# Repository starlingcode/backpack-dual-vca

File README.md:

# backpack-dual-vca
Dual 2164 VCA with precision 5V reference

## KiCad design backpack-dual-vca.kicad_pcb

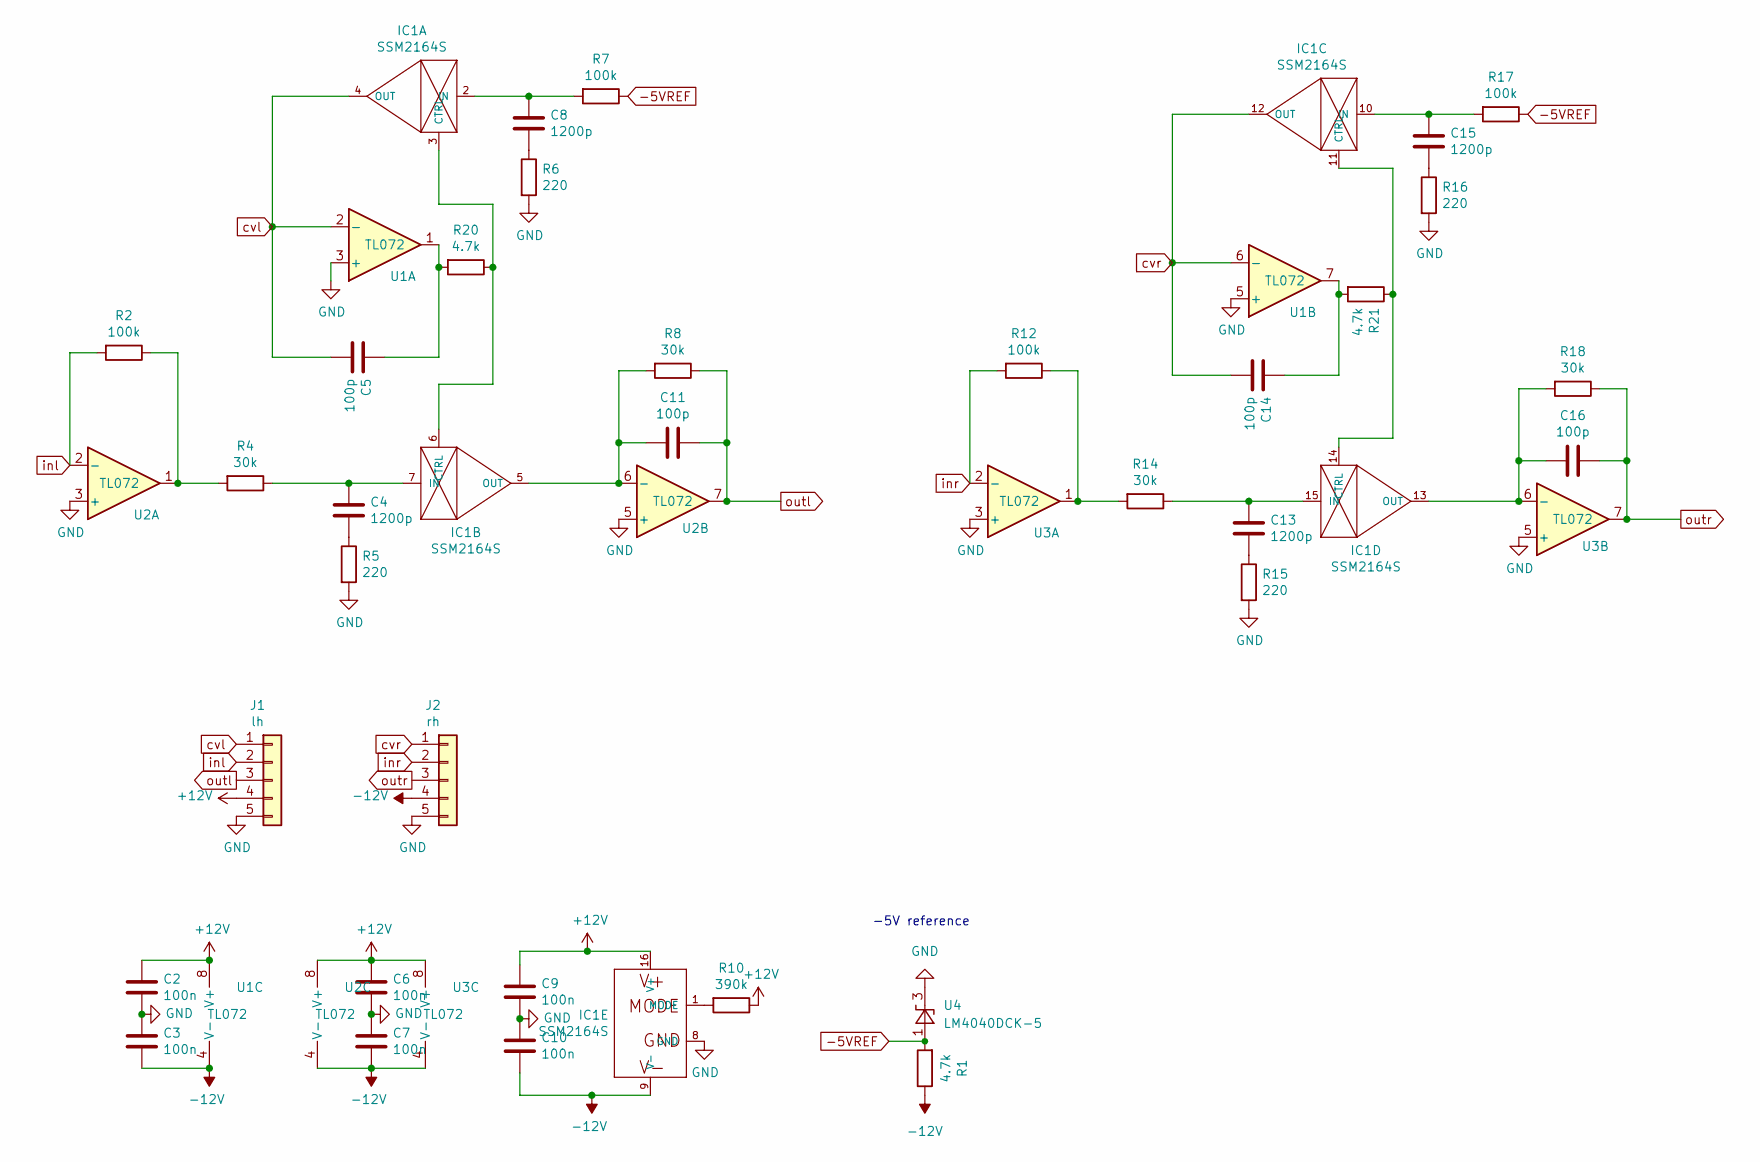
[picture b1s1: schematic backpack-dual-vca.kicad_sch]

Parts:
C2, C3, C6, C7, C9, C10: 100n; C_0402_1005Metric
C4, C8, C13, C15: 1200p; C_0402_1005Metric
C5, C11, C14, C16: 100p; C_0402_1005Metric
IC1: SSM2164S; SOIC-16_3.9x9.9mm_P1.27mm
J1: lh; PinSocket_1x05_P2.54mm_Vertical
J2: rh; PinSocket_1x05_P2.54mm_Vertical
R1, R20, R21: 4.7k; R_0402_1005Metric
R2, R7, R12, R17: 100k; R_0402_1005Metric
R4, R8, R14, R18: 30k; R_0402_1005Metric
R5, R6, R15, R16: 220; R_0402_1005Metric
R10: 390k; R_0402_1005Metric
U1, U2, U3: TL072; VSSOP-8_3.0x3.0mm_P0.65mm
U4: LM4040DCK-5; SOT-353_SC-70-5

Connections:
+12V: C2.1, C6.1, C9.1, IC1.16 (V+), J1.4, R10.1, U1.8 (V+), U2.8 (V+), U3.8 (V+)
-5VREF: R1.2, R7.1, R17.1, U4.1 (A)
-12V: C3.2, C7.2, C10.2, IC1.9 (V-), J2.4, R1.1, U1.4 (V-), U2.4 (V-), U3.4 (V-)
GND: C2.2, C3.1, C6.2, C7.1, C9.2, C10.1, IC1.8 (GND), J1.5, J2.5, R5.2, R6.2, R15.2, R16.2, U1.3 (+), U1.5 (+), U2.3 (+), U2.5 (+), U3.3 (+), U3.5 (+), U4.3 (K)
unnamed: C4.2, R5.1
unnamed: C5.1, R20.2, U1.1
unnamed: C8.2, R6.1
unnamed: C13.2, R15.1
unnamed: C14.1, R21.2, U1.7
unnamed: C15.2, R16.1
unnamed: IC1.3 (CTRL), IC1.6 (CTRL), R20.1
unnamed: C8.1, IC1.2 (IN), R7.2
unnamed: C4.1, IC1.7 (IN), R4.1
unnamed: C11.2, IC1.5 (OUT), R8.2, U2.6 (-)
unnamed: IC1.11 (CTRL), IC1.14 (CTRL), R21.1
unnamed: C15.1, IC1.10 (IN), R17.2
unnamed: C13.1, IC1.15 (IN), R14.1
unnamed: C16.2, IC1.13 (OUT), R18.2, U3.6 (-)
unnamed: IC1.1 (MODE), R10.2
unnamed: R2.1, R4.2, U2.1
unnamed: R12.1, R14.2, U3.1
cvl: C5.2, IC1.4 (OUT), J1.1, U1.2 (-)
cvr: C14.2, IC1.12 (OUT), J2.1, U1.6 (-)
inl: J1.2, R2.2, U2.2 (-)
inr: J2.2, R12.2, U3.2 (-)
outl: C11.1, J1.3, R8.1, U2.7
outr: C16.1, J2.3, R18.1, U3.7

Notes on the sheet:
-5V reference

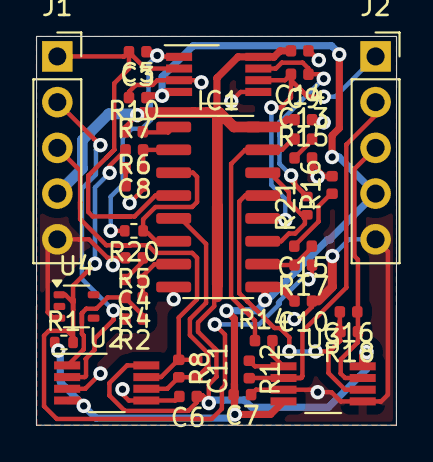
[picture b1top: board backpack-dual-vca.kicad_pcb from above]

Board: 2 copper layers, 20.0 x 21.6 mm, 37 parts (0 on the bottom side), 27 nets.

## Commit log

2024-11-15 Create LICENSE
2024-11-15 add backups folder to .gitignore
2024-11-15 removed cruft

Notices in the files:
backpack-dual-vca.kicad_pcb:
CC BY-NC-SA 4.0
